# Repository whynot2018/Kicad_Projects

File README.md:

# Kicad_Projects

### 1.25-15V 0-350mA bench power supply 
https://danyk.cz/minizdroj2_en.html

```
This is a simple linear bench DC voltage power supply with adjustable current limit. The output voltage can be set in the range of 1.25 to 15V and the current limitation 0 to 350mA. The voltage regulation uses well-known LM317 circuit. The current limiter uses a 0.3 ohm current sensing resistor (shunt). You can also use 0.27 or 0.33 ohm one. A 7812 circuit regulates the voltage for the OpAmp and also works as a voltage reference. The MC33171 OpAmp compares the shunt voltage to the voltage on the slider of the potentiometer. If the shunt voltage is higher, the OpAmp output will reduce the gate voltage of the MOSFET (FQP33N10) and thus limit the current. Current limiting mode is indicated by a red LED. In the power supply I used MYRRA 44268 transformer with 15V output voltage, 10VA power and 667mA maximum current. The output voltage at no load is approx. 18.3V. The bridge rectifier is made of SB340 or 1N5822 Schottky diodes to minimize the voltage drop. The 100k trimmer allows you to fine-tune the maximum adjustable current limit value, the 100 ohm trimmer the maximum adjustable output voltage. The LM317 circuit can be replaced with a compatible LM338 or LM350. It is also possible to use LM1084, LM1085 or LM1086, which have a lower dropout, but also a lower maximum input voltage (only 30V).
Warning! The device is powered from the mains. If constructed improperly, mains voltage can get to the output and cause an electric shock! It can also cause a fire. Capacitors can remain charged even after disconnected from mains. I do not guarantee the information provided. You do everything at your own risk. I take no responsibility for any damage. 
```

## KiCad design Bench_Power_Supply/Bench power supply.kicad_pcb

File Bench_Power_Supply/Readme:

### 1.25-15V 0-350mA bench power supply 
https://danyk.cz/minizdroj2_en.html

```
This is a simple linear bench DC voltage power supply with adjustable current limit. The output voltage can be set in the range of 1.25 to 15V and the current limitation 0 to 350mA. The voltage regulation uses well-known LM317 circuit. The current limiter uses a 0.3 ohm current sensing resistor (shunt). You can also use 0.27 or 0.33 ohm one. A 7812 circuit regulates the voltage for the OpAmp and also works as a voltage reference. The MC33171 OpAmp compares the shunt voltage to the voltage on the slider of the potentiometer. If the shunt voltage is higher, the OpAmp output will reduce the gate voltage of the MOSFET (FQP33N10) and thus limit the current. Current limiting mode is indicated by a red LED. In the power supply I used MYRRA 44268 transformer with 15V output voltage, 10VA power and 667mA maximum current. The output voltage at no load is approx. 18.3V. The bridge rectifier is made of SB340 or 1N5822 Schottky diodes to minimize the voltage drop. The 100k trimmer allows you to fine-tune the maximum adjustable current limit value, the 100 ohm trimmer the maximum adjustable output voltage. The LM317 circuit can be replaced with a compatible LM338 or LM350. It is also possible to use LM1084, LM1085 or LM1086, which have a lower dropout, but also a lower maximum input voltage (only 30V).
Warning! The device is powered from the mains. If constructed improperly, mains voltage can get to the output and cause an electric shock! It can also cause a fire. Capacitors can remain charged even after disconnected from mains. I do not guarantee the information provided. You do everything at your own risk. I take no responsibility for any damage. 
```

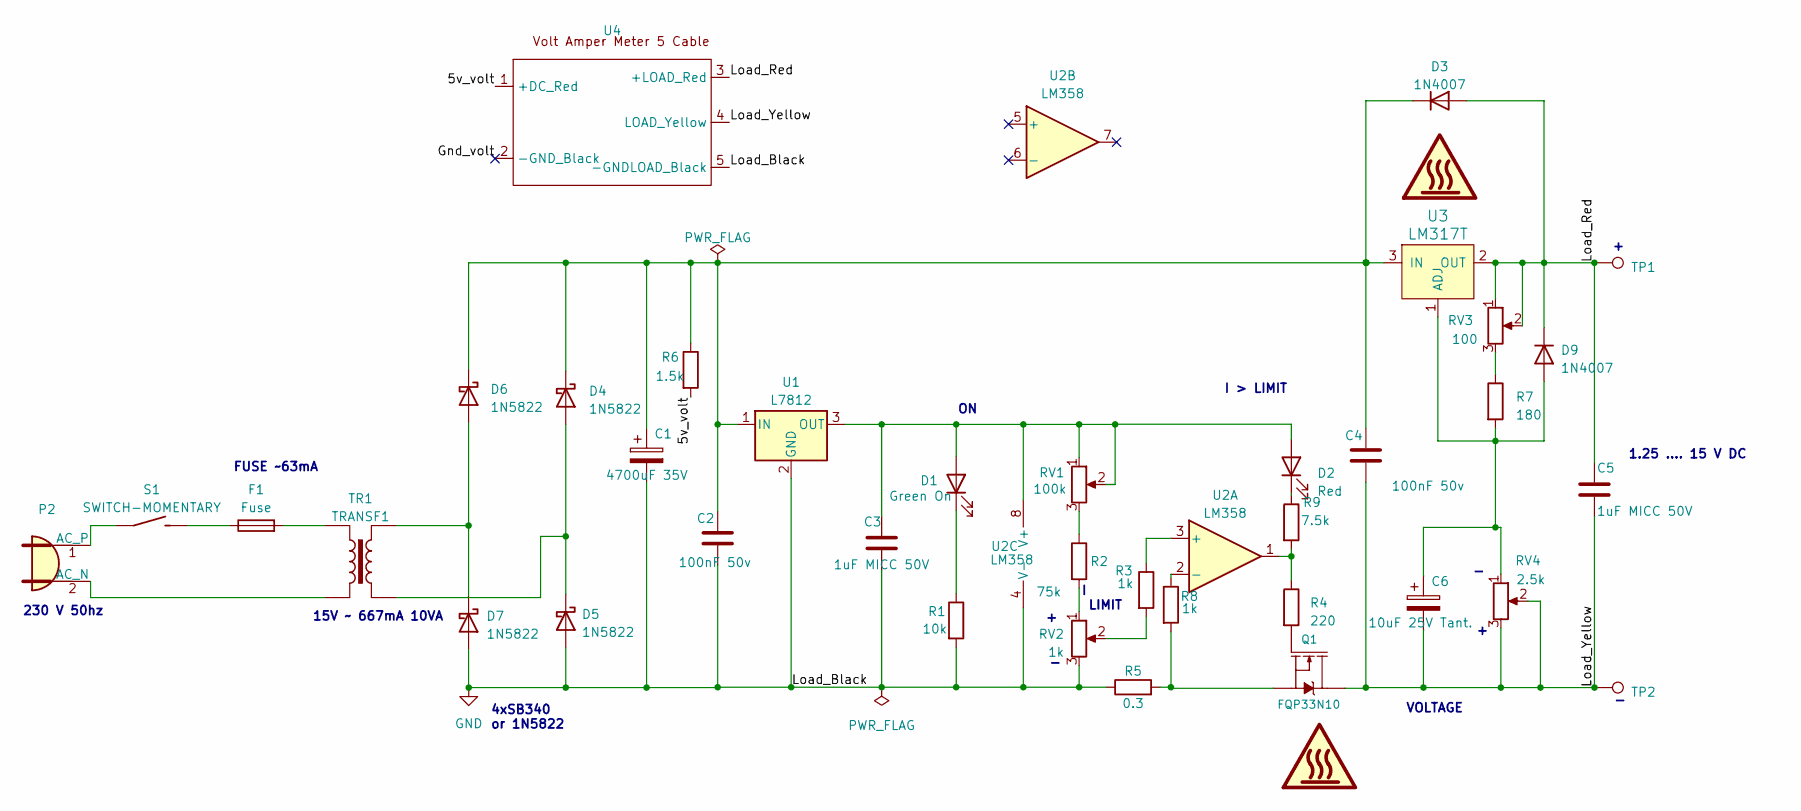
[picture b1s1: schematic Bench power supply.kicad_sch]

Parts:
C1: 4700uF 35V; CP_Radial_D8.0mm_P5.00mm
C2, C4: 100nF 50v; C_Disc_D7.5mm_W5.0mm_P7.50mm
C3, C5: 1uF MICC 50V; C_Disc_D7.5mm_W5.0mm_P7.50mm
C6: 10uF 25V Tant.; C_Disc_D8.0mm_W5.0mm_P5.00mm
D1: Green On; LED_D5.0mm
D2: Red; LED_D5.0mm
D3, D9: 1N4007; D_DO-41_SOD81_P10.16mm_Horizontal
D4, D5, D6, D7: 1N5822; D_DO-201AD_P15.24mm_Horizontal
F1: Fuse; Fuse_Littelfuse-LVR200
P2: Conn_WallPlug; TerminalBlock_bornier-2_P5.08mm
Q1: FQP33N10; TO220V
R1: 10k; R_Axial_DIN0414_L11.9mm_D4.5mm_P15.24mm_Horizontal
R2: 75k; R_Axial_DIN0414_L11.9mm_D4.5mm_P15.24mm_Horizontal
R3, R8: 1k; R_Axial_DIN0414_L11.9mm_D4.5mm_P15.24mm_Horizontal
R4: 220; R_Axial_DIN0414_L11.9mm_D4.5mm_P15.24mm_Horizontal
R5: 0.3; R_Axial_DIN0414_L11.9mm_D4.5mm_P15.24mm_Horizontal
R6: 1.5k; R_Axial_DIN0414_L11.9mm_D4.5mm_P15.24mm_Horizontal
R7: 180; R_Axial_DIN0414_L11.9mm_D4.5mm_P15.24mm_Horizontal
R9: 7.5k; R_Axial_DIN0414_L11.9mm_D4.5mm_P15.24mm_Horizontal
RV1: 100k; Potentiometer_ACP_CA9-H3,8_Horizontal
RV2: 1k; Potentiometer_ACP_CA9-H3,8_Horizontal
RV3: 100; Potentiometer_ACP_CA9-H3,8_Horizontal
RV4: 2.5k; Potentiometer_ACP_CA9-H3,8_Horizontal
S1: SWITCH-MOMENTARY; SW_CuK_OS102011MA1QN1_SPDT_Angled
TP1: +; TestPoint_THTPad_2.5x2.5mm_Drill1.2mm
TP2: -; TestPoint_THTPad_2.5x2.5mm_Drill1.2mm
TR1: TRANSF1; TRANSFORMER
U1: L7812; TO-220F-3_Vertical
U2: LM358; DIP-8_W7.62mm_LongPads
U3: LM317T; TO-220-3; MPN LM317T; Digi-Key_PN 497-1575-5-ND
U4: Volt_Amper_Meter_5_Cable

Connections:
/5v_volt: R6.2, U4.1 (+DC_Red)
/Gnd_volt: U4.2 (-GND_Black)
/Load_Red: C5.1, D3.2 (A), D9.1 (K), RV3.1, RV3.2, TP1.1, U3.2 (OUT), U4.3 (+LOAD_Red)
/Load_Yellow: C4.2, C5.2, C6.2, Q1.2 (D), RV4.2, RV4.3, TP2.1, U4.4 (LOAD_Yellow)
GND: C1.2, C2.2, C3.2, D5.2 (A), D7.2 (A), R1.2, R5.1, RV2.3, U1.2 (GND), U2.4 (V-), U4.5 (-GNDLOAD_Black)
unnamed: C1.1, C2.1, C4.1, D3.1 (K), D4.1 (K), D6.1 (K), R6.1, U1.1 (IN), U3.3 (IN)
unnamed: C3.1, D1.2 (A), D2.2 (A), RV1.1, RV1.2, U1.3 (OUT), U2.8 (V+)
unnamed: D1.1 (K), R1.1
unnamed: D2.1 (K), R9.1
unnamed: D4.2 (A), D5.1 (K), TR1.3
unnamed: D6.2 (A), D7.1 (K), TR1.4
unnamed: C6.1, D9.2 (A), R7.2, RV4.1, U3.1 (ADJ)
unnamed: F1.2, TR1.1
unnamed: P2.2 (AC_N), TR1.2
unnamed: P2.1 (AC_P), S1.1
unnamed: Q1.1 (G), R4.2
unnamed: Q1.3 (S), R5.2, R8.2
unnamed: R2.1, RV1.3
unnamed: R2.2, RV2.1
unnamed: R3.2, RV2.2
unnamed: R4.1, R9.2, U2.1
unnamed: R7.1, RV3.3
unnamed: F1.1, S1.3 (2)
unnamed: R3.1, U2.3 (+)
unnamed: R8.1, U2.2 (-)

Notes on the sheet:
15V ~ 667mA 10VA
FUSE ~63mA
VOLTAGE
4xSB340 or 1N5822
I > LIMIT
I LIMIT
230 V 50hz
1.25 .... 15 V DC

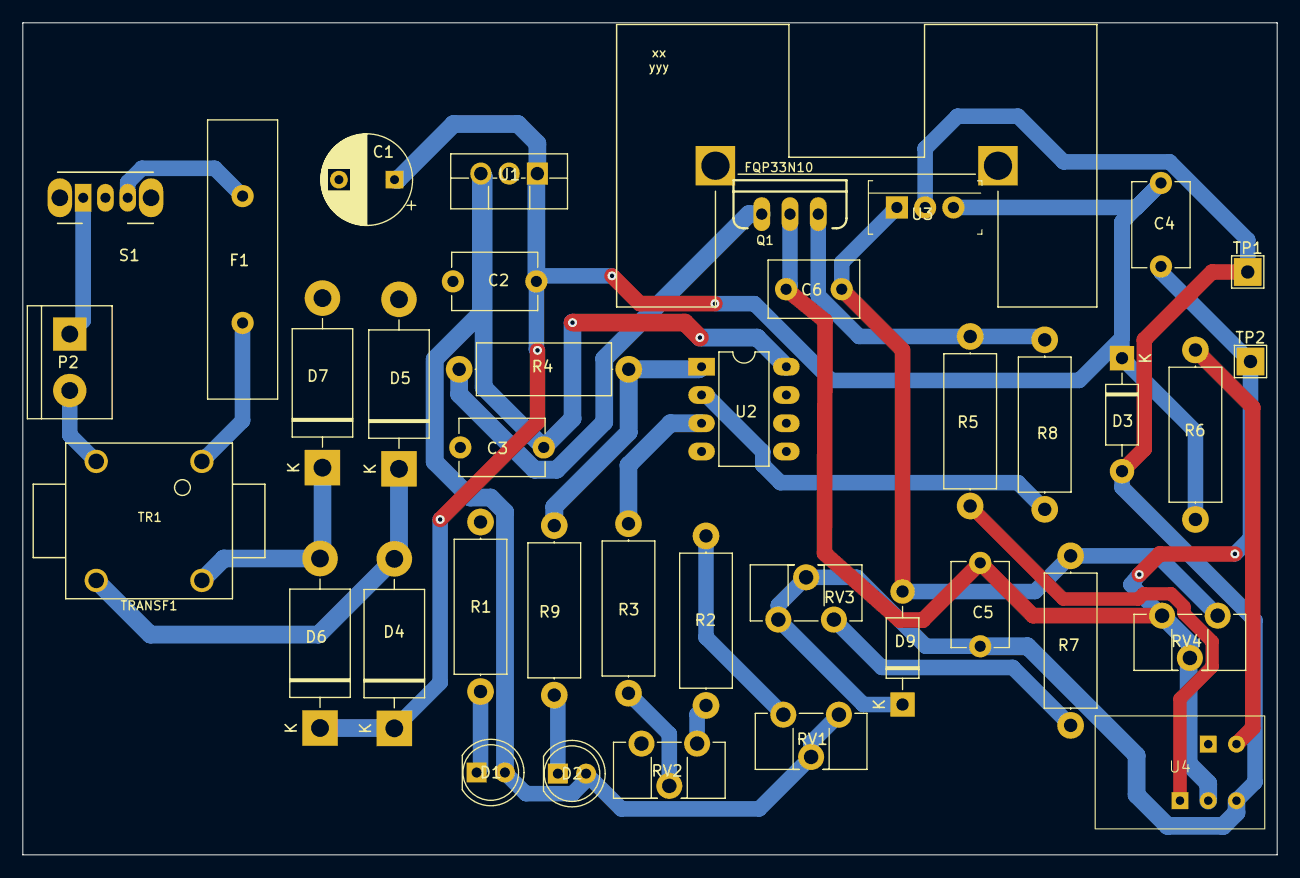
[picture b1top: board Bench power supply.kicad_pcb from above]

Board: 2 copper layers, 112.8 x 74.8 mm, 39 parts (0 on the bottom side), 24 nets.

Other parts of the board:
xx: yyy; HEATSINK_PRT-9576

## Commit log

2023-03-23 Create a
